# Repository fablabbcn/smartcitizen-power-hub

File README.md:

# SmartCitizen Power Hub

A simple board to distribute 5V and (in the future) control power outputs in Smart Citizen hardware setups

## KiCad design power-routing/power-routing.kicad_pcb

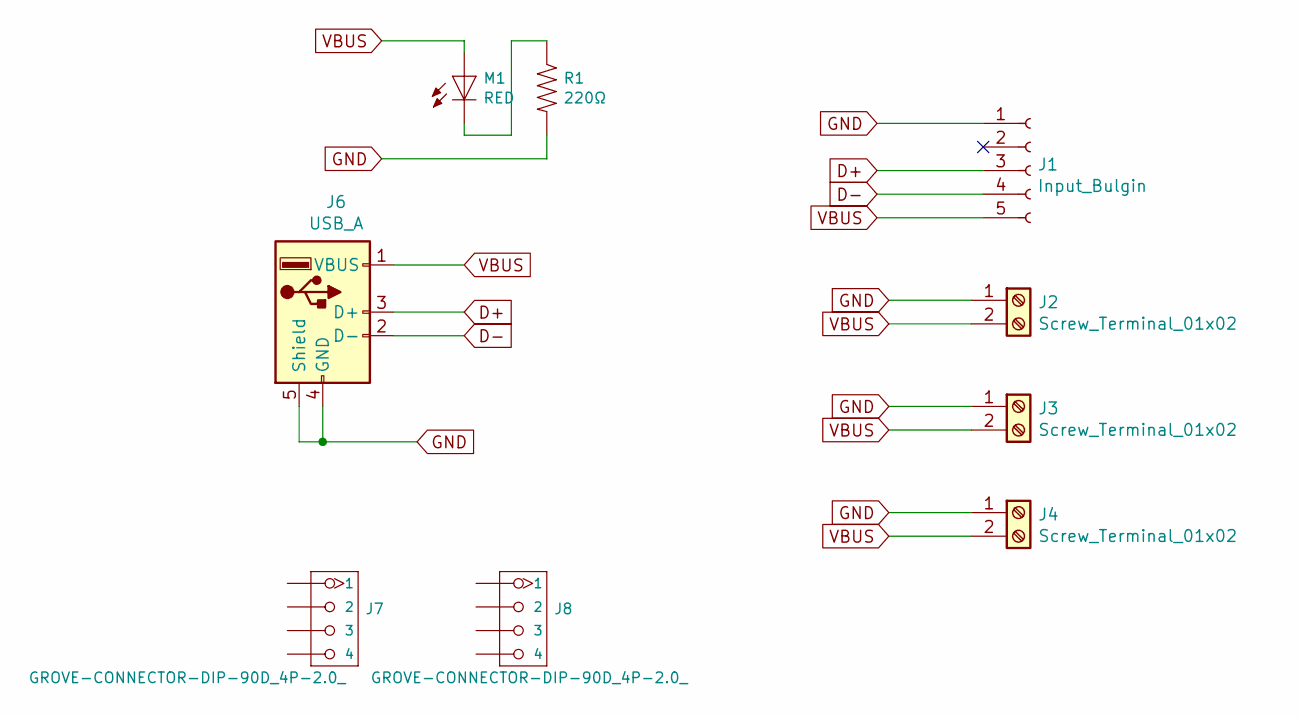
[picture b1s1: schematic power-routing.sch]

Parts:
J1: Input_Bulgin; PinHeader_1x05_P2.54mm_Vertical
J2, J3, J4: Screw_Terminal_01x02; TerminalBlock_Phoenix_PT-1,5-2-3.5-H_1x02_P3.50mm_Horizontal
J6: USB_A; USB_A_Amphenol_87520-1110BLF
J7, J8: GROVE-CONNECTOR-DIP-90D_4P-2.0_; HW4-SMD-2.0-90D
M1: RED; fab-LED1206FAB
R1: 220Ω; fab-R1206FAB

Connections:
D+: J1.3, J6.3 (D+)
D-: J1.4, J6.2 (D-)
GND: J1.1, J2.1, J3.1, J4.1, J6.4 (GND), J6.5 (Shield), R1.2
unnamed: M1.2 (C), R1.1
VBUS: J1.5, J2.2, J3.2, J4.2, J6.1 (VBUS), M1.1 (A)

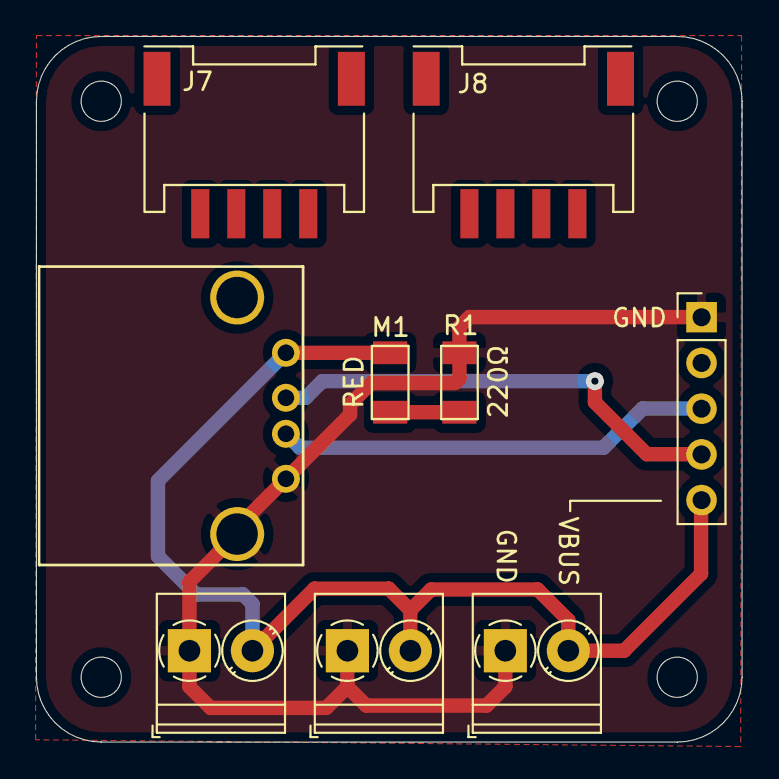
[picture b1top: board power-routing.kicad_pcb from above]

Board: 2 copper layers, 39.2 x 39.2 mm, 9 parts (0 on the bottom side), 5 nets.

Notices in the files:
power-routing/power-routing.kicad_pcb:
CERN OHL V1.0
